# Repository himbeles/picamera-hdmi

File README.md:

# picamera-hdmi

This is a board to convert the 15x1mm flat flex cable (FFC) from the Pi camera to (mini) HDMI, and from HDMI back to FFC on the Raspberry Pi side.

The purpose of this is to replace the fragile FFC connecting the Pi and the camera with a sturdier HDMI cable for "daily" camera use.
The design is inspired by [this extension board](https://shop.pimoroni.com/products/pi-camera-hdmi-cable-extension).

## Contents

This repository contains the KiCAD schematic, the PCB layout file for the adapter board and instructions for operation and assembly.

## Operation

The required parts for assembly are listed in the schematic, esentially 

- 2 boards
- a mini HDMI cable
- 2 Type 2 FFCs
- 2 mini HDMI and 2 FFC receptacles.

The FFC is inserted into the 15pin connector from one side and the 15 lanes are routed to a subset of the 19 HDMI lanes in a female mini HDMI receptacle.
The four differential data lanes from the camera are mapped to the four HDMI data lanes to preserve the signal quality over the length of the HDMI cable.

- To make sure all the lanes are correctly mapped, use Type 2 FFC (with contacts on opposing surfaces on both cable ends).
- On the camera side, plug the FFC with contacts down on the board.
- On the adapter side plug the FFC with contacts up.
- Same on the Raspberry Pi side. 

There are 4 M2 mounting holes for stacking the board onto the Pi Camera. 

The 4 remaining free lanes of the HDMI cable (13, 14, 17, 19) as well as the ground and 3.3V signals are broken out on the board for convenience.

## Make your own copy

A copy of our converter board can be ordered from OSH park:

<a href="https://oshpark.com/shared_projects/uJnKgfIw"></img></a>

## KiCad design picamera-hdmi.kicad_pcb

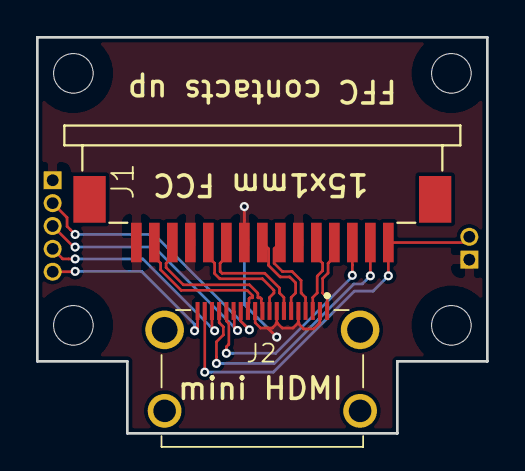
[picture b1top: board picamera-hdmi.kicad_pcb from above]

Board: 2 copper layers, 25.0 x 22.0 mm, 4 parts (0 on the bottom side), 16 nets.

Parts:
J1: FPC68611514122; 68611514122
J2: HDMI-685119136923; 685119136923
J3: Conn_01x05; PinHeader_1x05_P1.27mm_Vertical
J4: Conn_01x02; PinHeader_1x02_P1.27mm_Vertical

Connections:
+3V3: J1.1, J2.18, J4.2
/CAM-GPIO_N: J1.5, J2.3
/CAM-GPIO_P: J1.4, J2.1
/L2_N: J1.14, J2.12
/L2_P: J1.13, J2.10
/L3_N: J1.11, J2.9
/L3_P: J1.10, J2.7
/L4_N: J1.8, J2.6
/L4_P: J1.7, J2.4
/SCL: J1.3, J2.15
/SDA: J1.2, J2.16
/s13: J2.13, J3.2
/s14: J2.14, J3.3
/s17: J2.17, J3.4
/s19: J2.19, J3.5
Earth: J1.6, J1.9, J1.12, J1.15, J2.2, J2.5, J2.8, J2.11, J3.1, J4.1

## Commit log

2018-04-18 Add KiCad project
2018-04-19 more info in schematic
